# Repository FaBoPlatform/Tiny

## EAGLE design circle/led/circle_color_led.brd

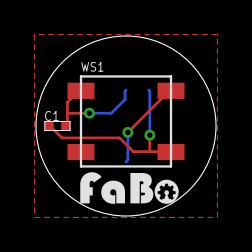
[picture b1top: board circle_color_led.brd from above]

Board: 2 copper layers, 10.0 x 10.0 mm, 4 parts (0 on the bottom side), 3 nets.

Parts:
C1: 0.1uf; 0402
U$2: FABO-NANO
U$3: LOGO_FABO_S
WS1: WS2818B

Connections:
+5V: C1.P$2, U$2.VCC, WS1.1
DI_1: U$2.2, WS1.4
GND: C1.P$1, U$2.GND, WS1.3

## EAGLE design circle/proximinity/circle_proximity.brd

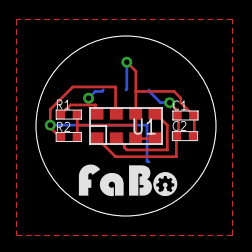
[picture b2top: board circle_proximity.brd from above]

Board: 2 copper layers, 10.0 x 10.0 mm, 7 parts (0 on the bottom side), 5 nets.

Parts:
C1, C2: 0.1uf; 0402
R1, R2: 4.7K; 0402
U1: VCNL4040M3OE
U$2: FABO-NANO
U$3: LOGO_FABO_S

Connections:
3V3: C1.P$2, C2.P$2, R1.P$2, R2.P$2, U1.3, U1.4, U1.6, U$2.VCC
GND: C1.P$1, C2.P$1, U1.1, U$2.GND
unnamed: U1.2, U1.5
SCL: R1.P$1, U1.8, U$2.0
SDA: R2.P$1, U1.7, U$2.1

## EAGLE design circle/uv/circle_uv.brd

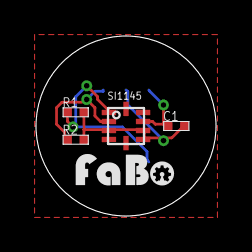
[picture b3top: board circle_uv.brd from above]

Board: 2 copper layers, 10.0 x 10.0 mm, 6 parts (0 on the bottom side), 4 nets.

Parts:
C1: 0.1uf; 0402
R1, R2: 4.7K; 0402
SI1145: SL-SI1145; SILICONLABS-SI1145
U$2: FABO-NANO
U$3: LOGO_FABO_S

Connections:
3V3: C1.P$2, R1.P$2, R2.P$2, SI1145.3, SI1145.6, SI1145.7, U$2.VCC
GND: C1.P$1, SI1145.8, U$2.GND
SCL: R2.P$1, SI1145.2, U$2.0
SDA: R1.P$1, SI1145.1, U$2.1

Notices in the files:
parts and their libraries:
FaBo-Template: Released under the Creative Commons Attribution-ShareAlike 4.0 License
https://creativecommons.org/licenses/by-sa/4.0
